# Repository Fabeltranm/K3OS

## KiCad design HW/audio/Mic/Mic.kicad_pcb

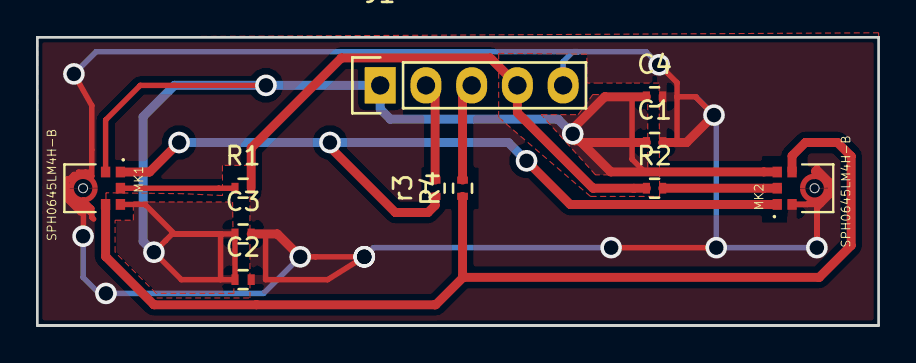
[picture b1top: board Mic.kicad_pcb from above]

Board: 2 copper layers, 46.7 x 16.0 mm, 11 parts (0 on the bottom side), 9 nets.

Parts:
C1, C2, C3, C4: C; R_0402
J1: Conn_01x05; Socket_Strip_Straight_1x05
MK1, MK2: SPH0645LM4H-B; MIC_SPH0645LM4H-B
R1, R2, R4: 51; R_0402
r3: 51; R_0402

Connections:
/bclk: MK1.4, MK2.4, R4.1
/data: J1.4, R1.2, R2.1
/ws: MK1.1, MK2.1, r3.1
GND: C1.2, C2.2, C3.2, C4.2, J1.5, MK1.3, MK2.2, MK2.3
unnamed: J1.2, r3.2
unnamed: J1.3, R4.2
unnamed: MK1.6, R1.1
unnamed: MK2.6, R2.2
VCC: C1.1, C2.1, C3.1, C4.1, J1.1, MK1.2, MK1.5, MK2.5

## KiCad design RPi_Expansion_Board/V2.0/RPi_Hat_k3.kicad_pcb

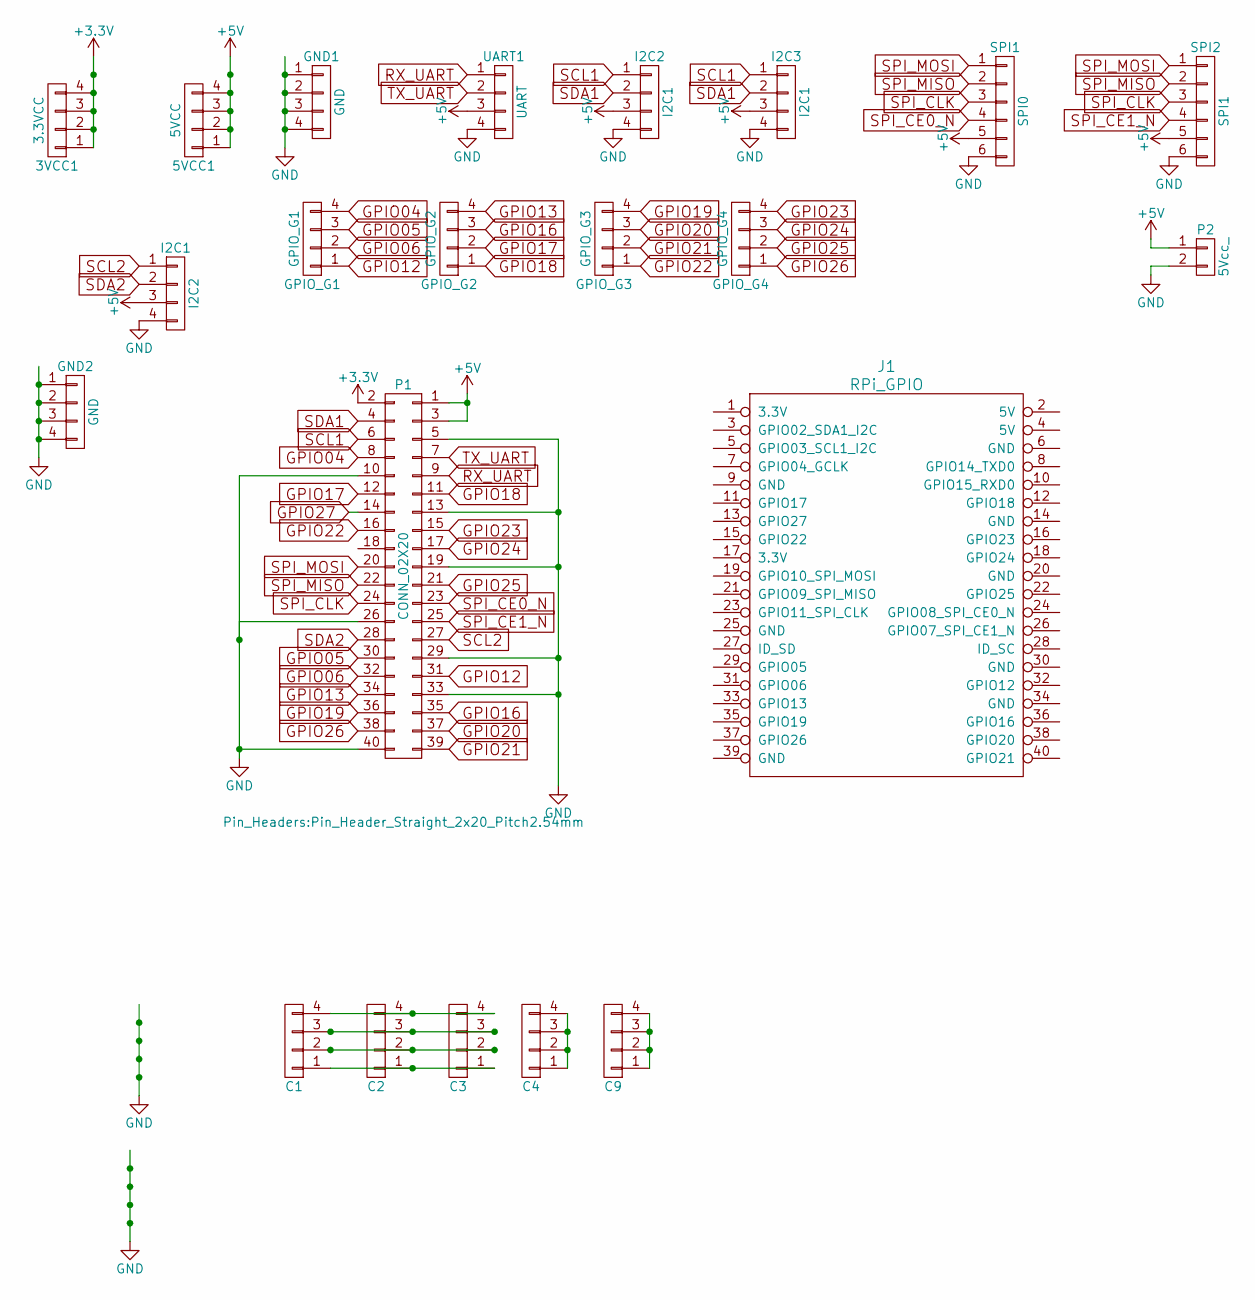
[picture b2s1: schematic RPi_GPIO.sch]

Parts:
3VCC1: 3.3VCC; Pin_Header_Straight_1x04_Pitch2.54mm
5VCC1: 5VCC; Pin_Header_Straight_1x04_Pitch2.54mm
C1, C2, C3, C4, C9: Pin_Header_Straight_1x04_Pitch2.54mm
GND1, GND2: GND; Pin_Header_Straight_1x04_Pitch2.54mm
GPIO_G1: GPIO_G1; Pin_Header_Straight_1x04_Pitch2.54mm
GPIO_G2: GPIO_G2; Pin_Header_Straight_1x04_Pitch2.54mm
GPIO_G3: GPIO_G3; Pin_Header_Straight_1x04_Pitch2.54mm
GPIO_G4: GPIO_G4; Pin_Header_Straight_1x04_Pitch2.54mm
I2C1: I2C2; Pin_Header_Straight_1x04_Pitch2.54mm
I2C2, I2C3: I2C1; Pin_Header_Straight_1x04_Pitch2.54mm
J1: RPi_GPIO
P1: CONN_02X20; Pin_Header_Straight_2x20_Pitch2.54mm
P2: 5Vcc_; Pin_Header_Angled_1x02_Pitch2.54mm
SPI1: SPI0; Pin_Header_Straight_1x06_Pitch2.54mm
SPI2: SPI1; Pin_Header_Straight_1x06_Pitch2.54mm
UART1: UART; Pin_Header_Straight_1x04_Pitch2.54mm

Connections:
+3V3: 3VCC1.1, 3VCC1.2, 3VCC1.3, 3VCC1.4, P1.2
+5V: 5VCC1.1, 5VCC1.2, 5VCC1.3, 5VCC1.4, I2C1.3, I2C2.3, I2C3.3, P1.1, P1.3, P2.1, SPI1.5, SPI2.5, UART1.3
GND: GND1.1, GND1.2, GND1.3, GND1.4, GND2.1, GND2.2, GND2.3, GND2.4, I2C1.4, I2C2.4, I2C3.4, P1.5, P1.10, P1.13, P1.19, P1.26, P1.29, P1.33, P1.40, P2.2, SPI1.6, SPI2.6, UART1.4
GPIO04: GPIO_G1.4, P1.8
GPIO05: GPIO_G1.3, P1.30
GPIO06: GPIO_G1.2, P1.32
GPIO12: GPIO_G1.1, P1.31
GPIO13: GPIO_G2.4, P1.34
GPIO16: GPIO_G2.3, P1.35
GPIO17: GPIO_G2.2, P1.12
GPIO18: GPIO_G2.1, P1.11
GPIO19: GPIO_G3.4, P1.36
GPIO20: GPIO_G3.3, P1.37
GPIO21: GPIO_G3.2, P1.39
GPIO22: GPIO_G3.1, P1.16
GPIO23: GPIO_G4.4, P1.15
GPIO24: GPIO_G4.3, P1.17
GPIO25: GPIO_G4.2, P1.21
GPIO26: GPIO_G4.1, P1.38
unnamed: C1.1, C2.1, C3.1
unnamed: C1.2, C2.2, C3.2
unnamed: C1.3, C2.3, C3.3
unnamed: C1.4, C2.4, C3.4
unnamed: C4.1, C4.2, C4.3, C4.4
unnamed: C9.1, C9.2, C9.3, C9.4
RX_UART: P1.9, UART1.1
SCL1: I2C2.1, I2C3.1, P1.6
SCL2: I2C1.1, P1.27
SDA1: I2C2.2, I2C3.2, P1.4
SDA2: I2C1.2, P1.28
SPI_CE0_N: P1.23, SPI1.4
SPI_CE1_N: P1.25, SPI2.4
SPI_CLK: P1.24, SPI1.3, SPI2.3
SPI_MISO: P1.22, SPI1.2, SPI2.2
SPI_MOSI: P1.20, SPI1.1, SPI2.1
TX_UART: P1.7, UART1.2

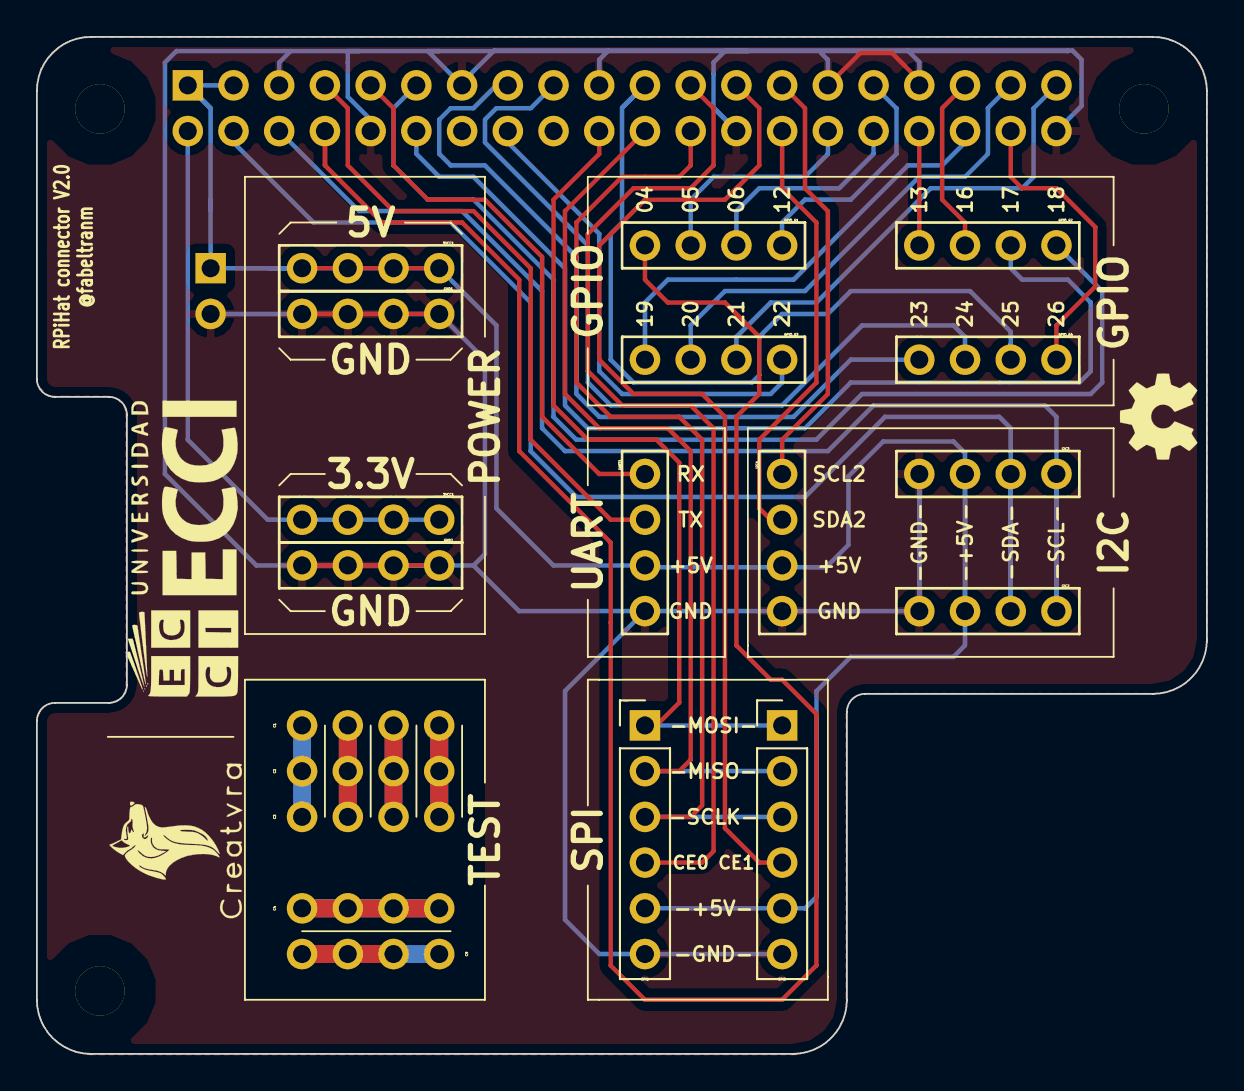
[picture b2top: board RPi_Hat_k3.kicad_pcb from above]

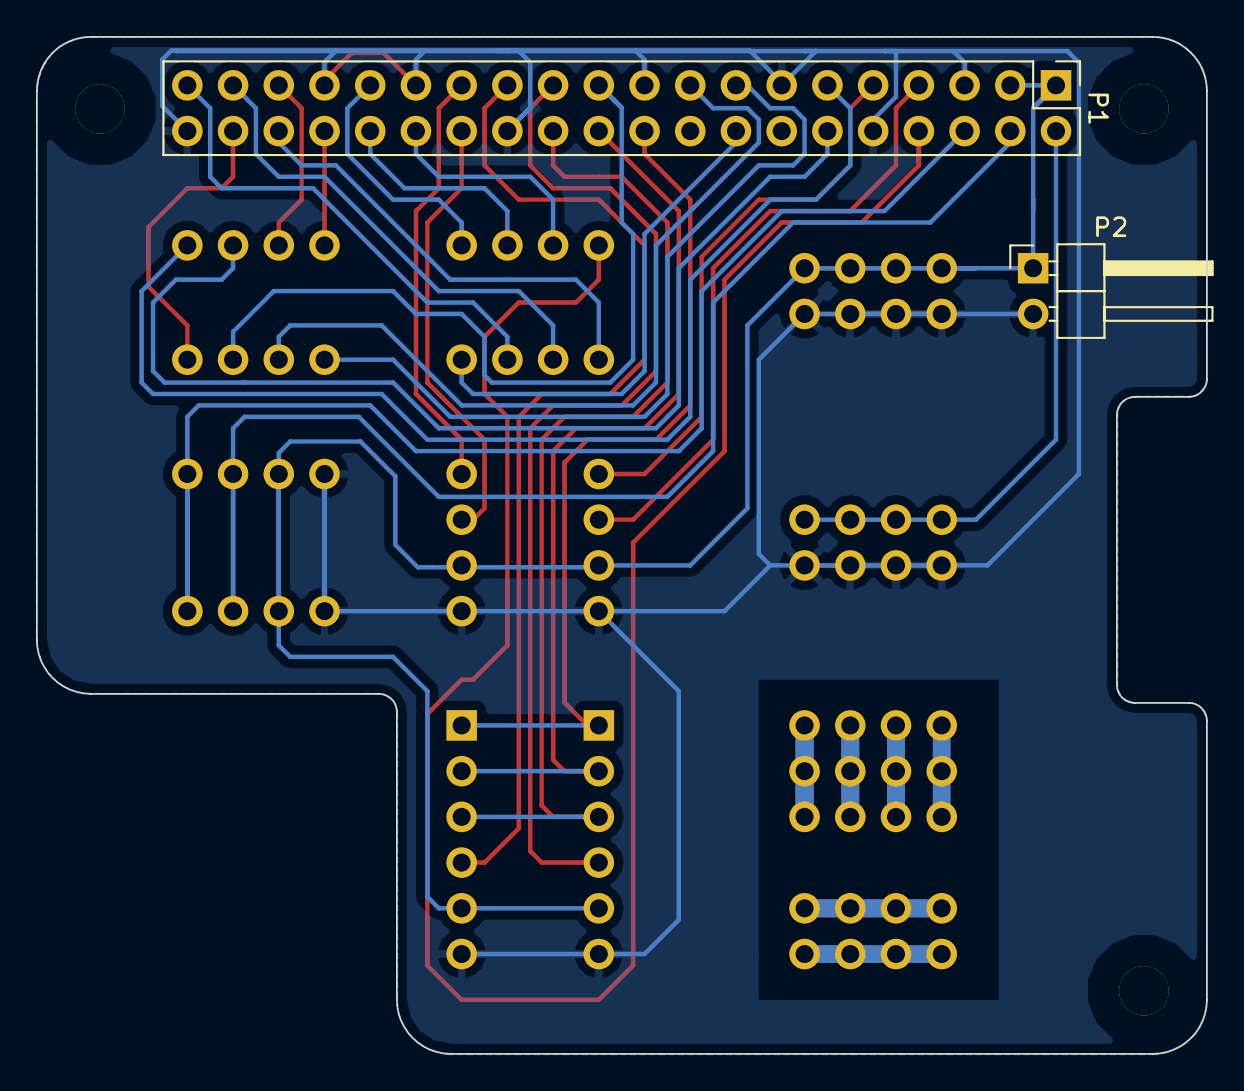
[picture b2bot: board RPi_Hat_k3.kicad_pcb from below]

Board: 2 copper layers, 65.0 x 56.5 mm, 21 parts (2 on the bottom side), 36 nets.

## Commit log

2017-03-23 V0.9
2017-03-23 v1.0
2017-03-23 model 3d
2017-04-08 RPi Hat V2
2017-04-22 include logos
2017-04-22 gerber
2017-04-22 delated p
2017-04-26 cambios en clamp
    modificacion V2 al clamp
2017-04-26 Revert "cambios en clamp"
    This reverts commit a5dcf231417c90a1c8c8961c6481be991a881ba8.
2017-04-26 modificacion gerber clamp
2017-04-26 subida de archivos V2
2017-04-26 Add files via upload
    resubida de archivo con cambio en el diametro de un orificio
2017-04-28 Nueva version con el header alineado al centro
2017-04-28 actualizacion con ambas board separadas
2017-05-02 cambios en los gerber de la tarjeta expansion
2017-05-03 cambios en la board de expansion RPI
2017-05-03 cambios RPI board
2017-05-03 cambios en los archivos gerber de la tarjeta RPI
2017-05-03 Cambios de la PCB
2017-05-04 cambios en la RPI expansion board y logos
2017-05-04 drill
2017-05-04 cambiops
2017-05-04 cambios
2017-05-04 cambios en archivos gerber de la expansion RPI
2017-05-04 cambios en los gerber de la RPI expansion
2017-05-04 cambios Gerber RPI expansion
2017-05-05 cambios en tarjeta clamp
2017-05-05 ajuste
2017-05-16 Update readme.m and example
2017-05-23 cambios gerber k3
2017-05-23 ejemplo foto para RPI con Ultrasonido
2017-06-02 add pro
2017-06-20 Update cabezote
2017-07-10 cofig files and dir
2017-07-10 config dir and files
2017-07-10 Ultimas modificaciones en los archivos gerber de tarjeta CLAMP
2017-07-12 add audio
2017-07-31 add planos finales de corte laser
2017-11-20 Se agrega PCB para MIC I2S SPH0645LM4H-B
2018-04-07 imagen fondo de pantalla para k3os
2018-07-03 nuevo diseño 1.1
